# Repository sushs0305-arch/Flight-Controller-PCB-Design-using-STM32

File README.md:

# Flight-Controller-PCB-Design-using-STM32
Custom 2-layer flight controller PCB designed using KiCad based on the STM32F405RGTx microcontroller for drone and embedded robotics applications.
STM32 Flight Controller PCB

# **STM32 Flight Controller PCB**

## **Overview**

A custom STM32-based flight controller PCB designed for drone and embedded robotics applications using a compact 2-layer architecture. The board integrates motion sensing, GPS communication, compass and barometer support, USB connectivity, power regulation, and debugging interfaces for real-time embedded control systems.

* * *

# **System Architecture**

The flight controller includes:

## **Processing Unit**
- STM32F405RGTx microcontroller
- High-performance ARM Cortex-M4 core
- Real-time sensor processing and control

## **Motion Sensing Unit**
- MPU6050 IMU
  - Accelerometer
  - Gyroscope
- Sensor fusion support for orientation tracking

## **Navigation Support**
- GPS module interface
  - GPS_RX
  - GPS_TX
- Compass interface support
- Barometer interface support for altitude sensing

## **Communication Interfaces**
- USB communication interface
- SWD debugging header
- I2C communication support
- UART communication support

## **Power Management**
- AMS1117-3.3V regulator
- Ferrite bead filtering
- Decoupling capacitors
- Stable power distribution network

* * *

# **PCB Design**

## **Design Features**
- Compact 2-layer PCB
- Optimized signal routing
- Ground plane implementation
- DRC verified layout
- Mounting hole support
- Sensor-oriented placement strategy

## **Design Tools**
- KiCad
- STM32
- Embedded Hardware Design

* * *

# **Project Gallery**

## **Schematic Design**
(
)

## **PCB Layout**
(
)

## **3D PCB View**
(
)

* * *

# **Working Principle**

The STM32 microcontroller collects real-time motion and navigation data from the IMU, GPS, compass, and barometer interfaces. The processed sensor data can be used for stabilization, navigation, orientation estimation, and autonomous control in drone and robotics systems.

* * *

# **System Design Advantages**

## **Compact Design**
- Small form factor suitable for embedded applications

## **Modular Interfaces**
- Easy integration with external sensors and modules

## **Expandability**
- Supports additional peripherals through UART and I2C

## **Reliable Power Design**
- Stable 3.3V regulation and filtered supply rails

## **Debugging Support**
- SWD interface for firmware development and testing

* * *

# **Applications**

- Drone Flight Controllers
- Robotics Systems
- Autonomous Navigation Systems
- Embedded Sensor Fusion Projects

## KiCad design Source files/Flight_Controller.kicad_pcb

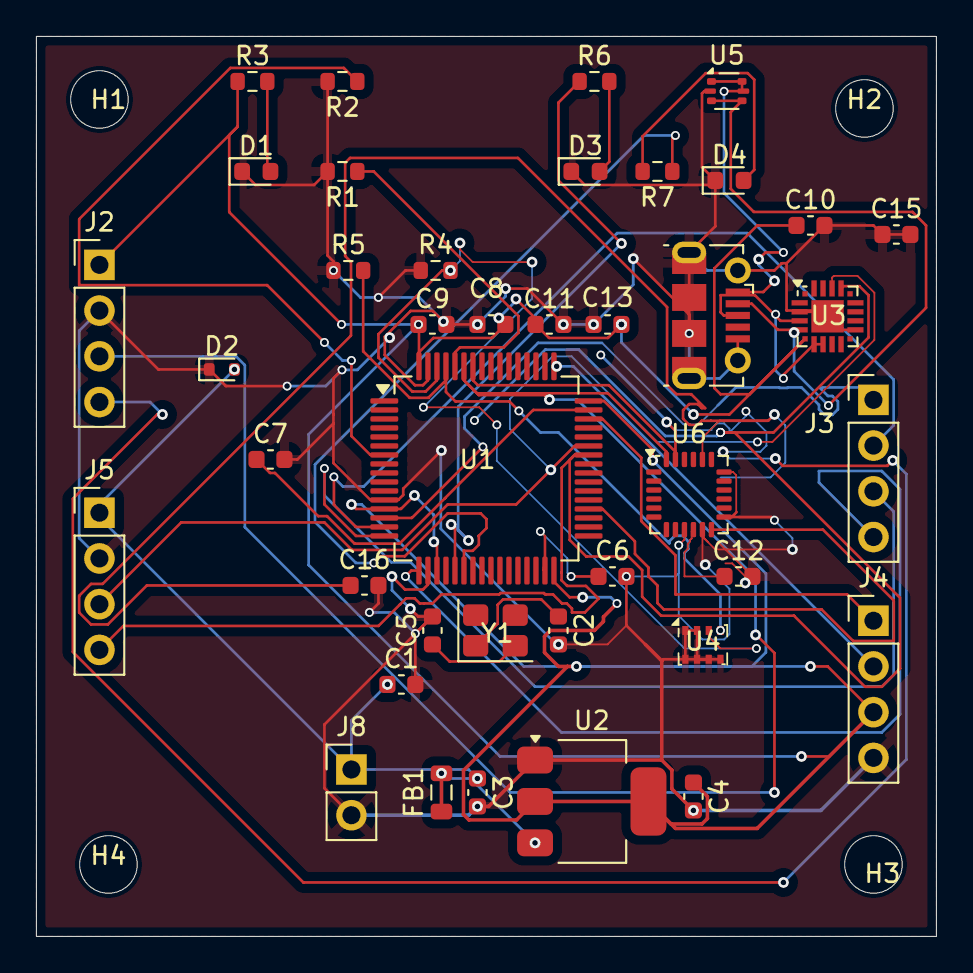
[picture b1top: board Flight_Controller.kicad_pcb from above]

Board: 2 copper layers, 50.0 x 50.0 mm, 44 parts (0 on the bottom side), 31 nets.

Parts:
C1: 100uF; C_0603_1608Metric
C2, C5: 22pF; C_0603_1608Metric
C3, C4: 10uF; C_0603_1608Metric
C6, C7: 2.2uF; C_0603_1608Metric
C8, C9, C10, C11, C12, C13, C15: 0.1uF; C_0603_1608Metric
C16: 2.2nF; C_0603_1608Metric
D1, D3, D4: LED; LED_0603_1608Metric
D2: ESD5Zxx; D_SOD-523
FB1: FerriteBead; L_0805_2012Metric
H1, H2, H3, H4: MountingHole; MountingHole_3.2mm_M3
J2: I2C_COMPASS; PinHeader_1x04_P2.54mm_Vertical
J3: PWM OUTPUT; PinHeader_1x04_P2.54mm_Vertical
J4: SWD HEADER; PinHeader_1x04_P2.54mm_Vertical
J5: GPS HEADER; PinHeader_1x04_P2.54mm_Vertical
J6: USB_B_Micro; USB_Micro-B_Molex-105017-0001
J8: BATTERY CONNECTOR; PinHeader_1x02_P2.54mm_Vertical
R1, R2: 10K; R_0603_1608Metric
R3, R6, R7: 330; R_0603_1608Metric
R4, R5: 4.7K; R_0603_1608Metric
U1: STM32F405RGTx; LQFP-64_10x10mm_P0.5mm
U2: AMS1117-3.3; SOT-223-3_TabPin2
U3: CP2102N-Axx-xQFN20; SiliconLabs_QFN-20-1EP_3x3mm_P0.5mm_EP1.8x1.8mm
U4: BMP280; Bosch_LGA-8_2x2.5mm_P0.65mm_ClockwisePinNumbering
U5: USBLC6-2P6; SOT-666
U6: MPU-6050; InvenSense_QFN-24_4x4mm_P0.5mm
Y1: Crystal; Crystal_SMD_3225-4Pin_3.2x2.5mm

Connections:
/3V3: C4.1, C8.1, C9.1, C10.1, C11.1, C13.1, J2.1, J4.3, R3.1, U1.13 (VDDA), U1.19 (VDD), U1.32 (VDD), U1.48 (VDD), U1.64 (VDD), U2.2 (VO), U3.6 (VDD)
/5V_IN: C1.1, C3.1, D2.2 (A), FB1.1, FB1.2, J5.1, J8.1, U2.3 (VI)
/GPS_RX: J5.4, U1.42 (PA9), U3.17 (RXD)
/GPS_TX: J5.3, U1.43 (PA10), U3.18 (TXD)
/M1: J3.1, U1.14 (PA0)
/M2: J3.2, U1.15 (PA1)
/M3: J3.3, U1.16 (PA2)
/M4: J3.4, U1.17 (PA3)
/OSC_IN: C2.1, Y1.1
/OSC_OUT: C5.1, Y1.2
/PA15: U1.36 (PB15), U6.12 (INT)
/SCL: J2.4, U1.58 (PB6), U6.23 (SCL)
/SDA: J2.3, U1.59 (PB7), U6.24 (SDA)
/SWCLK: J4.2, U1.49 (PA14)
/SWDIO: J4.1, U1.46 (PA13)
GND: C1.2, C2.2, C3.2, C4.2, C5.2, C6.2, C7.2, C8.2, C9.2, C10.2, C11.2, C12.2, C13.2, C15.1, C15.2, C16.2, D1.1 (K), D2.1 (K), D3.1 (K), D4.1 (K), J2.2, J4.4, J5.2, J6.5 (GND), J6.6 (Shield), J8.2, R1.2, R2.2, R4.1, R5.1, U1.12 (VSSA), U1.18 (VSS), U1.63 (VSS), U2.1 (GND), U3.3 (GND), U3.12 (GND), U3.21 (GND), U4.1 (GND), U4.2 (CSB), U4.5 (SDO), U4.6 (VDDIO), U4.7 (GND), U4.8 (VDD), U5.2 (GND), U6.9 (AD0), U6.11 (FSYNC), U6.13 (VDD), U6.18 (GND)
unnamed: D1.2 (A), R3.2
unnamed: D3.2 (A), R6.2
unnamed: D4.2 (A), R7.2
unnamed: J6.1 (VBUS), J6.3 (D+), U3.4 (D+), U3.7 (VREGIN), U3.8 (VBUS), U5.1 (I/O1), U5.5 (VBUS), U5.6 (I/O1)
unnamed: J6.2 (D-), U3.5 (D-), U5.3 (I/O2), U5.4 (I/O2)
unnamed: R1.1, U1.60 (BOOT0)
unnamed: R2.1, U1.7 (NRST)
unnamed: R6.1, U1.21 (PA5)
unnamed: R7.1, U1.22 (PA6)
unnamed: R5.2, U1.61 (PB8), U4.4 (SCK)
unnamed: R4.2, U1.62 (PB9), U4.3 (SDI)
unnamed: C6.1, U1.31 (VCAP_1)
unnamed: C7.1, U1.47 (VCAP_2)
unnamed: C16.1, U6.20 (CPOUT)
unnamed: C12.1, U6.10 (REGOUT)
